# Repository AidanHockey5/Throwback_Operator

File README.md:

# THROWBACK OPERATOR
OPL3 VGM player powered by STM32

This project is a hardware video game music (VGM) player that uses a genuine YMF262 (OPL3) sound chip and its accompanying YAC512 DAC.
There is no emulation here. This is the real chip.

Included in this repository is the complete schematic, firmware source, and KiCAD board files. Feel free to make your own board, but please don't resell them :)

If you would like to purchase an official complete Throwback Operator board, you can order one from me here: https://www.aidanlawrence.com/product/throwback-operator/

# Information About the Main Sound Chips and VGM

The YMF262, also known as the Operator Type L3 (OPL3), is an 18-channel FM sound chip that was commonly found inside of personal computers in the mid to late 1990's.
Most notably, the OPL3 was found on the Sound Blaster Pro 2 and the Sound Blaster 16.
The OPL3 is backwards compatible with the OPL2 (YM3812). The OPL2 is backwards compatible with the original OPL (YM3526).
This means that the Throwback Operator is capable of playing back OPL3, OPL2, and OPL tracks. The OPL2 was found on the original Adlib and Sound Blaster cards.
The OPL was usually found within arcade machines.

The clock signal for the YMF262 is dynamically generated from the microcontroller. The timers on this particular board only have 16-bit resolution, so VGMs with exotic frequencies may not sound perfectly in tune. Standard clock OPL2 and OPL3 VGMs will often sound just fine though.

VGM stands for Video Game Music, and it is a 44.1KHz logging format that stores real sound chip register information. My player will parse these files and send the data to the appropriate chips. You can learn more about the VGM file format here: http://www.smspower.org/Music/VGMFileFormat

http://www.smspower.org/uploads/Music/vgmspec170.txt?sid=58da937e68300c059412b536d4db2ca0

# Schematic

# SD Card Information

The Throwback Operator accepts MicroSD cards formatted as FAT32. Your SD card must only contain uncompressed .vgm files. VGZ FILES WILL NOT WORK! You may download .vgz files and use 7zip to extract the uncompressed file out of them. Vgm files on the SD card do not need to have the .vgm extension. As long as they contain valid, uncompressed vgm data, they will be read by the program regardless of their name. You can find VGM files by Googling "myGameName VGM," or by checking out sites like http://vgmrips.net/packs/

# Control Over Serial
You can use a serial connection to control playback features. The commands are as follows:

Command | Result
------------ | -------------
\+ | Next Track
\- | Previous Track
\* | Random Track
\/ | Toggle Shuffle Mode
\. | Toggle Song Looping
r: | Request song
? | What song is playing?
\! | Toggle the OLED display

A song request is formatted as follows: ```r:mySongFile.vgm```
Once a song request is sent through the serial console, an attempt will be made to open that song file. The file must exist on the SD card, and spelling/capitalization must be correct.
Need an easy-to-use serial console? [I've made one here.](https://github.com/AidanHockey5/OpenArduinoSerialConsole)

# Programming the Microcontroller

The on-board microcontroller is a STM32F103C8T6, the same microcontroller found on the popular "blue pill" development boards. 
Therefore, programming the Throwback Operator boards is fairly similar.
The firmware was built with Visual Studio Code with the PlatformIO extension installed.

Programming over Serial:
* Connect your Throwback Operator board to your computers USB port.
* Ensure that you have the CH340 driver installed. Windows 10 should have this automatically, otherwise, [grab the driver here](https://sparks.gogo.co.nz/ch340.html)
* Ensure nothing else is currently connected to your board over serial.
* On the top of the board, you will see two black jumpers. By default, these jumpers are both in the "Down" position (middle pin and bottom pin jumped).
* Remove the left jumper and reattach it to the "Up" position (middle pin and top pin jumped).
* Press the RESET button on the Throwback Operator board

* You can either program the device with the flashing tool linked below, or from the source code.

[DOWNLOAD THE FLASHING TOOL HERE](https://www.aidanlawrence.com/tools/ee/tbo/Megaflasher_Throwback_Operator.zip)

* Windows users are reccomended to run the pre-compiled "Flash.exe" file.
  All other operating system users must run the Flash.py file. 
  Dependancies and instructions are listed in the Readme file.
* After successfully running the flashing tool, you are done and don't need to continue with the following instructions.

If you plan to build from the source code instead:
* In VS Code (or whatever your IDE of choice is), navigate to the `platformio.ini` and ensure the upload protocol is set to `serial`
* Hit the upload button (Arrow icon in the bottom bar of VS code)
* Once your code is uploaded, replace the left jumper to its original "Down" position 

# Troubleshooting

Occasionally, when the player is first plugged in, it will hang or get caught in a boot-loop. Plugging in a USB cable gives breif moments of unstable power when the contacts inside of the connector are jostling against eachother which may place the SD card in an unknown state. Simply disconnect and reconnect the USB cable if you are caught in a bootloop.

This player is for OPL-family VGMs only. That means you can play any VGM file that contains data for the YM3526 (OPL), YM3812 (OPL2) or the YMF262 (OPL3).

Ensure that your VGM files are uncompressed. VGZ files will not work. Simply use 7zip on VGM files to extract the VGM files within.

Make sure your SD card is formatted to FAT32 and only contains VGM files. Folders are not supported.

# Looking for an Enclosure for your Player?

Voodle has contributed a 3D-printable enclosure for the Throwback Operator!
https://www.thingiverse.com/thing:4577831

Thanks, Voodle!

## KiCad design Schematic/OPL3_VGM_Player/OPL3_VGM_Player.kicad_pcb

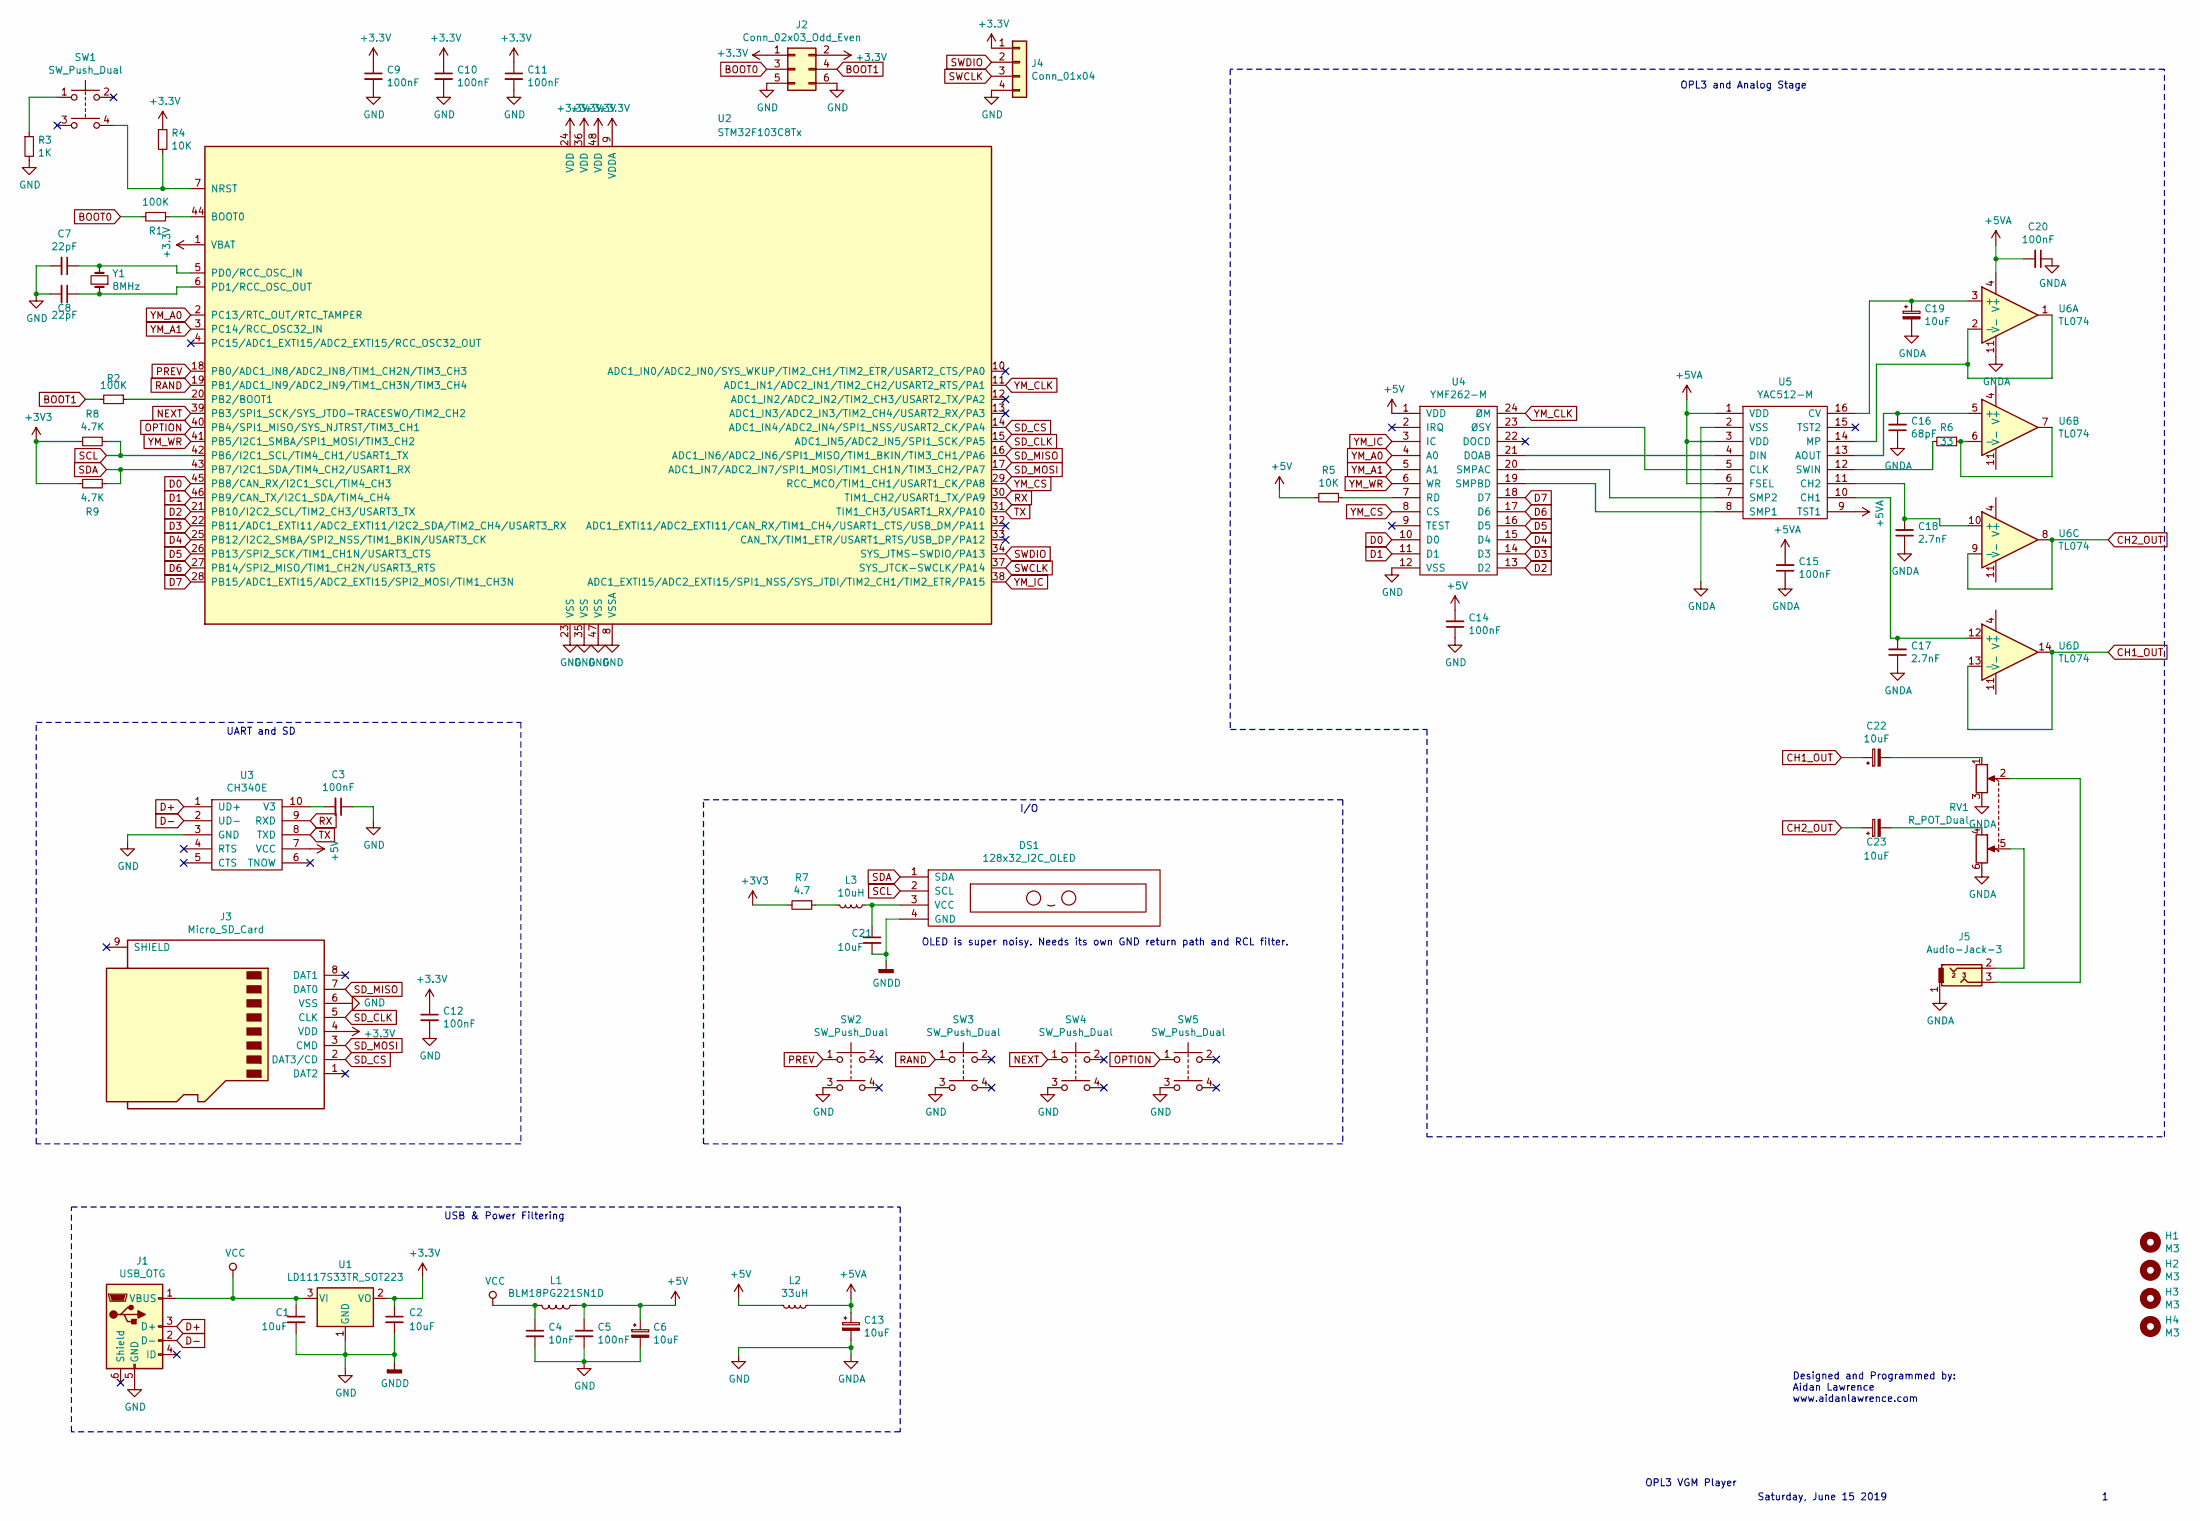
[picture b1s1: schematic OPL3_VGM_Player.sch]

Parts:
C1, C2, C21: 10uF; C_1206
C3, C5, C9, C10, C11, C12, C14, C15, C20: 100nF; C_0805
C4: 10nF; C_0805
C6, C13, C19, C22, C23: 10uF; CP_Elec_3x5.3
C7, C8: 22pF; C_0603
C16: 68pF; C_0603
C17, C18: 2.7nF; C_0603
DS1: 128x32_I2C_OLED; 128x32_OLED_I2C_Module
H1, H2, H3, H4: M3; MountingHole_3.2mm_M3
J1: USB_OTG; USB_Mini-B
J2: Conn_02x03_Odd_Even; Pin_Header_Straight_2x03_Pitch2.54mm
J3: Micro_SD_Card; SOFNG_TF_15x15_PUSH_PUSH
J4: Conn_01x04; Pin_Header_Straight_1x04_Pitch2.54mm
J5: Audio-Jack-3; SWITCHCRAFT_35RAPC4BHN2
L1: BLM18PG221SN1D; L_0603
L2: 33uH; L_4x4
L3: 10uH; L_4x4
R1, R2: 100K; R_0805
R3: 1K; R_0805
R4, R5: 10K; R_0805
R6: 33; R_0805
R7: 4.7; R_0805
R8, R9: 4.7K; R_0805
RV1: R_POT_Dual; Potentiometer_Alps_RK097_Double_Vertical
SW1, SW2, SW3, SW4, SW5: SW_Push_Dual; SW_TH_Tactile_Omron_B3F-10xx
U1: LD1117S33TR_SOT223; SOT-223-3_TabPin2
U2: STM32F103C8Tx; LQFP-48_7x7mm_Pitch0.5mm
U3: CH340E; MSOP-10_3x3mm_Pitch0.5mm
U4: YMF262-M; SOIC-24W_7.5x15.4mm_Pitch1.27mm
U5: YAC512-M; SOIC-16W_5.3x10.2mm_Pitch1.27mm
U6: TL074; SOIC-14_3.9x8.7mm_Pitch1.27mm
Y1: 8MHz; Crystal_SMD_HC49-SD

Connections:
+5V: C5.1, C6.1, C14.2, L1.1, L2.2, R5.2, U3.7 (VCC), U4.1 (VDD)
+5VA: C13.1, C15.2, C20.2, L2.1, U5.1 (VDD), U5.3 (VDD), U5.6 (FSEL), U5.9 (TST1), U6.4 (V+)
BOOT0: J2.3, R1.2
BOOT1: J2.4, R2.2
CH1_OUT: C22.1, U6.13 (-), U6.14
CH2_OUT: C23.1, U6.8, U6.9 (-)
D0: U2.45 (PB8/CAN_RX/I2C1_SCL/TIM4_CH3), U4.10 (D0)
D1: U2.46 (PB9/CAN_TX/I2C1_SDA/TIM4_CH4), U4.11 (D1)
D2: U2.21 (PB10/I2C2_SCL/TIM2_CH3/USART3_TX), U4.13 (D2)
D3: U2.22 (PB11/ADC1_EXTI11/ADC2_EXTI11/I2C2_SDA/T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), U4.14 (D3)
D4: U2.25 (PB12/I2C2_SMBA/SPI2_NSS/TIM1_BKIN/USART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), U4.15 (D4)
D5: U2.26 (PB13/SPI2_SCK/TIM1_CH1N/USART3_CTS), U4.16 (D5)
D6: U2.27 (PB14/SPI2_MISO/TIM1_CH2N/USART3_RTS), U4.17 (D6)
D7: U2.28 (PB15/ADC1_EXTI15/ADC2_EXTI15/SPI2_MOSI/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), U4.18 (D7)
D+: J1.3 (D+), U3.1 (UD+)
D-: J1.2 (D-), U3.2 (UD-)
NEXT: SW4.1, U2.39 (PB3/SPI1_SCK/SYS_JTDO-TRACESWO/TIM2_CH2)
unnamed: C3.2, U3.10 (V3)
unnamed: C7.1, U2.5 (PD0/RCC_OSC_IN), Y1.2
unnamed: C8.1, U2.6 (PD1/RCC_OSC_OUT), Y1.1
unnamed: C16.2, U5.13 (AOUT), U6.5 (+)
unnamed: C17.2, U5.10 (CH1), U6.12 (+)
unnamed: C18.2, U5.11 (CH2), U6.10 (+)
unnamed: C19.1, U5.16 (CV), U6.3 (+)
unnamed: C21.1, DS1.3 (VCC), L3.1
unnamed: C22.2, RV1.1
unnamed: C23.2, RV1.4
unnamed: J5.2, RV1.5
unnamed: J5.3, RV1.2
unnamed: L3.2, R7.1
unnamed: R1.1, U2.44 (BOOT0)
unnamed: R2.1, U2.20 (PB2/BOOT1)
unnamed: R3.1, SW1.1
unnamed: R4.2, SW1.4, U2.7 (NRST)
unnamed: R5.1, U4.7 (RD)
unnamed: R6.1, U6.6 (-), U6.7
unnamed: R6.2, U5.12 (SWIN)
unnamed: U4.19 (SMPBD), U5.8 (SMP1)
unnamed: U4.20 (SMPAC), U5.7 (SMP2)
unnamed: U4.21 (DOAB), U5.4 (DIN)
unnamed: U4.23 (ØSY), U5.5 (CLK)
unnamed: U5.14 (MP), U6.1, U6.2 (-)
OPTION: SW5.1, U2.40 (PB4/SPI1_MISO/SYS_NJTRST/TIM3_CH1)
PREV: SW2.1, U2.18 (PB0/ADC1_IN8/ADC2_IN8/TIM1_CH2N/TIM3_CH3)
RAND: SW3.1, U2.19 (PB1/ADC1_IN9/ADC2_IN9/TIM1_CH3N/TIM3_CH4)
RX: U2.30 (TIM1_CH2/USART1_TX/PA9), U3.9 (RXD)
SCL: DS1.2 (SCL), R8.1, U2.42 (PB6/I2C1_SCL/TIM4_CH1/USART1_TX)
SDA: DS1.1 (SDA), R9.1, U2.43 (PB7/I2C1_SDA/TIM4_CH2/USART1_RX)
SD_CLK: J3.5 (CLK), U2.15 (ADC1_IN5/ADC2_IN5/SPI1_SCK/PA5)
SD_CS: J3.2 (DAT3/CD), U2.14 (ADC1_IN4/ADC2_IN4/SPI1_NSS/USART2_CK/PA4)
SD_MISO: J3.7 (DAT0), U2.16 (ADC1_IN6/ADC2_IN6/SPI1_MISO/TIM1_BKIN/T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)
SD_MOSI: J3.3 (CMD), U2.17 (ADC1_IN7/ADC2_IN7/SPI1_MOSI/TIM1_CH1N/T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)
SWCLK: J4.3, U2.37 (SYS_JTCK-SWCLK/PA14)
SWDIO: J4.2, U2.34 (SYS_JTMS-SWDIO/PA13)
TX: U2.31 (TIM1_CH3/USART1_RX/PA10), U3.8 (TXD)
VCC: C1.1, C4.1, J1.1 (VBUS), L1.2, U1.3 (VI)
YM_A0: U2.2 (PC13/RTC_OUT/RTC_TAMPER), U4.4 (A0)
YM_A1: U2.3 (PC14/RCC_OSC32_IN), U4.5 (A1)
YM_CLK: U2.11 (ADC1_IN1/ADC2_IN1/TIM2_CH2/USART2_RTS/P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), U4.24 (ØM)
YM_CS: U2.29 (RCC_MCO/TIM1_CH1/USART1_CK/PA8), U4.8 (CS)
YM_IC: U2.38 (ADC1_EXTI15/ADC2_EXTI15/SPI1_NSS/SYS_JT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), U4.3 (IC)
YM_WR: U2.41 (PB5/I2C1_SMBA/SPI1_MOSI/TIM3_CH2), U4.6 (WR)

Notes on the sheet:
Designed and Programmed by: Aidan Lawrence www.aidanlawrence.com
OPL3 VGM Player
Saturday, June 15 2019
OLED is super noisy. Needs its own GND return path and RCL filter.
USB & Power Filtering
UART and SD
I/O
OPL3 and Analog Stage

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
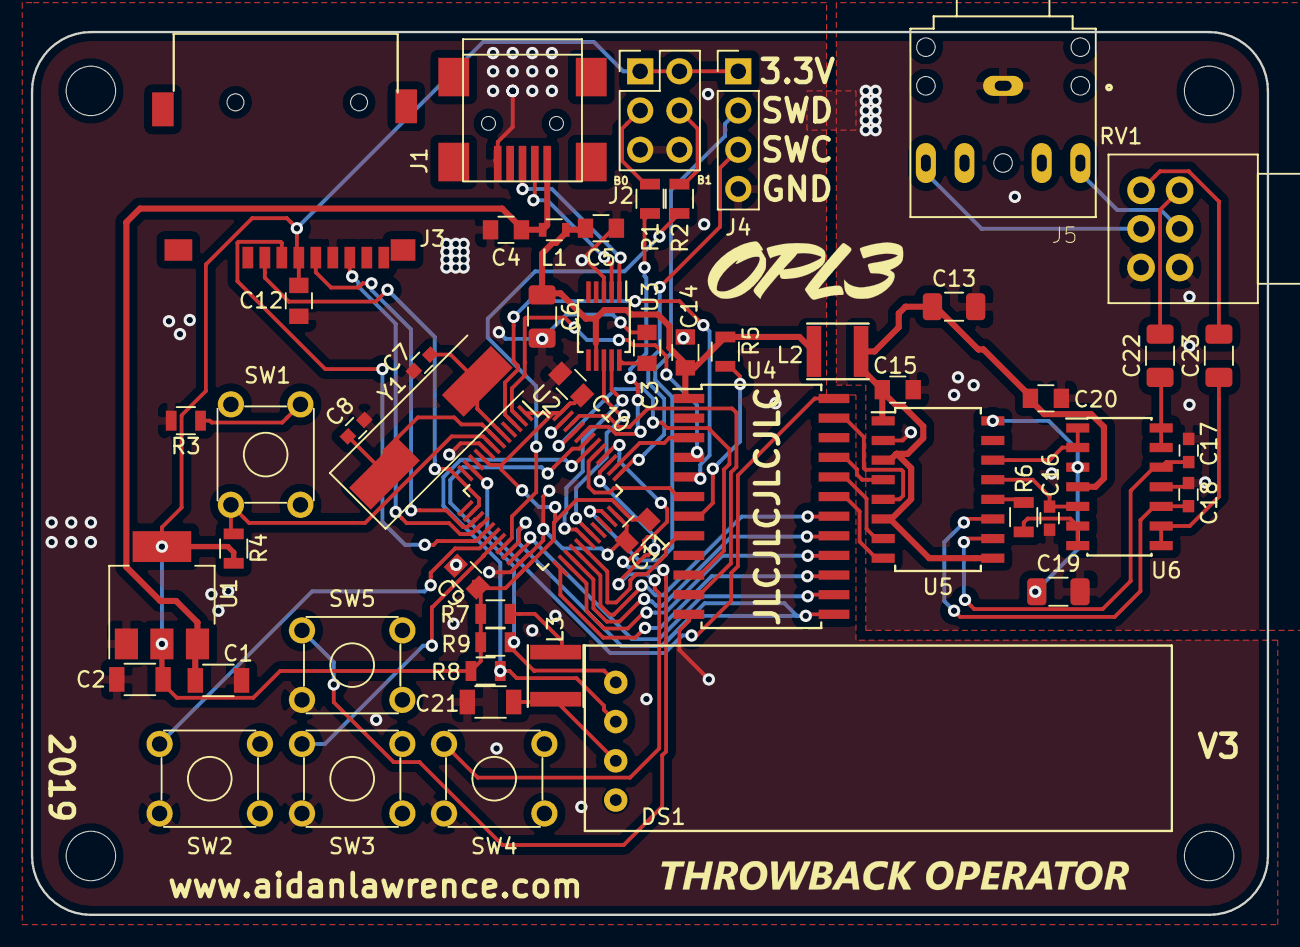
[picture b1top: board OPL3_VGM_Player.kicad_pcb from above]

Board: 2 copper layers, 80.0 x 57.2 mm, 58 parts (0 on the bottom side), 64 nets.

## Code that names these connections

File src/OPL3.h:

#ifndef __OPL3_H__
#define __OPL3_H__
#include <Arduino.h>

class OPL3
{
private:
    uint8_t IC = PA15;
    uint8_t CS = PA8;
    uint8_t A0 = PC13;
    uint8_t A1 = PC14;
    uint8_t WR = PB5;

public:
    OPL3(/* args */);
    ~OPL3();
    void Send(uint8_t addr, uint8_t data, bool setA1);
    void SetOPLMode(bool isOPL3);
    void Reset();
};


#endif

/*
PB8   -   D0
PB9   -   D1
PB10 -   D2
PB11 -   D3
PB12 -   D4
PB13 -   D5
PB14 -   D6
PB15 -   D7

PC13   -   A0
PC14   -   A1

PB5   -  WR
PULLED HIGH   -  RD

PA15   -   IC
PA8 -   CS
*/

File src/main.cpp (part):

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
//Debug variables
//REMOVE IN PCB VERSION
#define ENABLE_DEBUG_PORT_PIN PB3 //If this pin is HIGH, enable the debug port pins, otherwise, disable the pins. Keep pin low by default. Disables STlink when low.
//REMOVE IN PCB VERSION
#define DEBUG false //Set this to true for a detailed printout of the header data & any errored command bytes
#define DEBUG_LED PC15
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//PlayMode playMode = PlayMode::IN_ORDER;

//IO
const uint8_t next_btn = PB3;
const uint8_t prev_btn = PB0;
const uint8_t rand_btn = PB1;
const uint8_t option_btn = PB4;

//OLED
U8G2_SSD1306_128X32_UNIVISION_F_SW_I2C u8g2(U8G2_R0, PB6, PB7, U8X8_PIN_NONE); //SW I2C for now, HW seems to have a bug that crashes the unit
bool isOledOn = true;

void setup()
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  //DISABLE DEBUG BY DEFAULT IN PCB VERSION!!!
  disableDebugPorts();

  //Output OPL3 clock on PA1
  /****configure clocks for PORTA & TIMER2********/
  RCC_BASE->APB2ENR |= RCC_APB2ENR_IOPAEN; // enable port A clock
  RCC_BASE->APB1ENR |= RCC_APB1ENR_TIM2EN; // enable clock for timer 2
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  pinMode(option_btn, INPUT_PULLUP);

  //SD
  while(!SD.begin(PA4, SPI_HALF_SPEED)) 
  {
    SD.begin(PA4, SPI_HALF_SPEED);
    delay(100);
    u8g2.clearBuffer();
    u8g2.drawStr(0,16,"SD Mount");
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
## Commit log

2019-05-10 Made some timers, chip drivers, you know, that kinda thing
2019-05-10 Porting YM2612 VGM player
2019-05-10 saving
2019-05-12 Driver now outputs OPL2/3 music.
2019-05-13 OPL3 now fully operational in both OPL2/3 modes
2019-05-13 Minor OPL2/3 switch fix
2019-05-29 UART serial instead of native USB. Add OLED
2019-06-16 Begin schematic
2019-06-16 Saving work on schematic. IO Pin Changes
2019-06-17 Schematic plotted
2019-06-17 Footprints
2019-06-18 PCB first pass
2019-06-19 PCB Complete
2019-06-25 Modify firmware for PCB
2019-06-28 Automatic clock adjustment
2019-07-11 Draft readme
2019-07-11 README programming instructions
2019-07-13 Added schematic images and pdf
2019-08-05 new wdt and sd init
2019-08-05 New meta file removal. No more annoying MacOS meta files!
2019-08-11 Create LICENSE
2019-08-11 Rename LICENSE to LICENSE.md
2019-08-29 Minor change to headphone jack
2019-10-07 SMD caps and fixed headphone jack pin sizes
2021-01-04 New VGM engine
2021-01-04 PCM and extra chip ignores
2021-01-05 Added flashing tool
